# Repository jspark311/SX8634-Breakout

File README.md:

# SX8634-Breakout

A breakout board for Semtech's SX8634 capacitive touch sensor.

#### [Hackaday.io Page](https://hackaday.io/project/166853-sx8634-touch-sensor-breakout)

#### [Order from Tindie](https://www.tindie.com/products/17862/)

#### [Arduino driver](https://github.com/jspark311/Arduino-SX8634)

------------------------

### What is in this repository:

**./doc**:  Location for documentation

**./KiCAD**:  Hardware design files

**./lib**:  Third-party libraries

**./main**:  The optional provisioning program

**./downloadDeps.sh**   A script to download dependencies

------------------------

### Building the provisioning program

The provisioning program is intended to be run on an ESP32 devkit-C or comparable. It can be built by doing...

    ./downloadDeps.sh
    make

Then, flash it to the ESP32 board....

    make flash monitor

------------------------

Front | Back
:-------:|:------:
  |

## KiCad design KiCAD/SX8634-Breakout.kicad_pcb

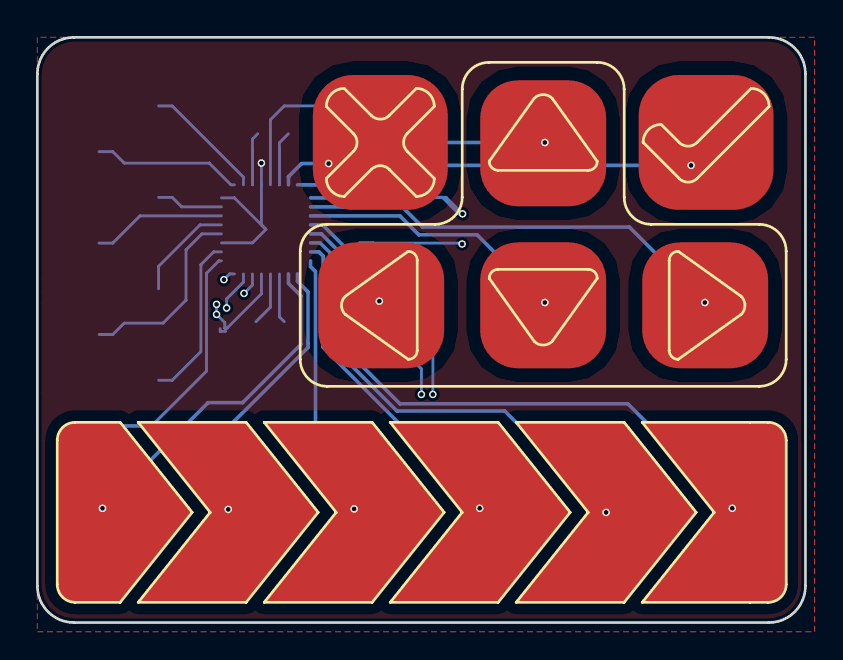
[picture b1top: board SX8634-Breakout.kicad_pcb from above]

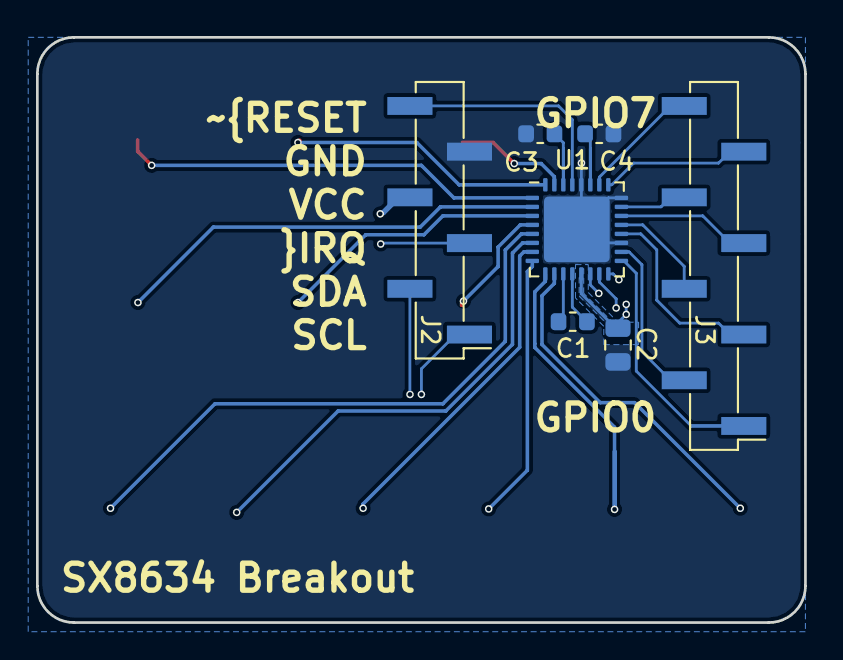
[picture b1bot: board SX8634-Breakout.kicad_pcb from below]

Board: 4 copper layers, 42.7 x 32.5 mm, 9 parts (7 on the bottom side), 30 nets.

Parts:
C1: 1nF; C_0603_1608Metric
C2: 100uF; C_0805_2012Metric
C3, C4: 100nF; C_0603_1608Metric
J1: Conn_01x12_Male; Cap-Touch_pattern_compact
J2: Conn_01x06; PinHeader_1x06_P2.54mm_Vertical_SMD_Pin1Left
J3: Conn_01x08; PinHeader_1x08_P2.54mm_Vertical_SMD_Pin1Left
P1: CONN_01X01; ManuvrLogo
U1: SX8634; QFN-32-1EP_5x5mm_P0.5mm_EP3.65x3.65mm

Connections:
/GPIO0: J3.1, U1.17
/GPIO1: J3.2, U1.18
/GPIO2: J3.3, U1.20
/GPIO3: J3.4, U1.21
/GPIO4: J3.5, U1.22
/GPIO5: J3.6, U1.23
/GPIO6: J3.7, U1.25
/GPIO7: J3.8, U1.26
/I2C_SCL: J2.1, U1.15
/I2C_SDA: J2.2, U1.16
/VCC: C2.1, J2.4, U1.13
/cap0: J1.6, U1.31
/cap1: J1.1, U1.32
/cap2: J1.5, U1.1
/cap3: J1.4, U1.2
/cap4: J1.2, U1.3
/cap5: J1.3, U1.4
/cap6: J1.12, U1.5
/cap7: J1.11, U1.6
/cap8: J1.10, U1.7
/cap9: J1.9, U1.8
/cap10: J1.8, U1.9
/cap11: J1.7, U1.10
/~Touch_IRQ: J2.3, U1.14
/~Touch_Reset: J2.6, U1.29
GND: C2.2, C3.1, C4.1, J2.5, U1.19, U1.24, U1.28, U1.33
unnamed: C1.1, U1.12
unnamed: C1.2, U1.11
unnamed: C3.2, U1.30
unnamed: C4.2, U1.27

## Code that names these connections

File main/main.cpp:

/**
* SX8634 provisioner
*
* This is Ian's tool for provisioning and testing Manuvr's touch boards. It is
*   being provided to inform the efforts of intrepid users who want to burn a
*   customized configuration to their board's non-volatile memory (NVM).
*
* This process is only needed if...
*   1) The GPIO pins are used as inputs, and the circuit can't abide pin contention.
*   2) The default settings are in some other way inadequate and instant-on is desired.
*
* If these cases don't apply to a given application, the boards can be used as-is.
* The only thing special about this program are the build-time options...
* #define CONFIG_MANUVR_SX8634         // Needed in any application using the touch board.
* #define CONFIG_SX8634_PROVISIONING   // Only needed to provision.
*
* A finished application would use CONFIG_MANUVR_SX8634, and possibly also
*   CONFIG_SX8634_CONFIG_ON_FAITH.
*
* CONFIG_SX8634_CONFIG_ON_FAITH causes the driver to skip the step of reading
*   the configuration from the chip on every boot. During this time, the chip
*   will be unresponsive to touch, and most applications will already know what
*   the loaded configuration will be. Using this option requires the config to
*   be provided to the driver during instantiation. The program will fail at
*   runtime if this configuration is not provided.
*
* Burning the NVM requires that the part be run a little bit hotter than the
*   rest of the system (3.6v). So the hardware needs to respect that fact also.
*   Trying to burn the NVM outside of this voltage range doesn't appear to cause
*   any damage, but it won't actually burn the NVM, and the chip won't tell you
*   why it failed. So it's on the user to ensure the voltage is adequate.
* The provisioning hardware level-shifts the GPIO pins for the sake of testing
*   the boards.
*
* Pins
* -------------
* IO33   SX8634 reset pin via level-shifter
* IO35   SX8634 IRQ pin via level-shifter with 3.3v pullup
* IO32   SCL
* IO25   SDA
*
* IO23   3.6v regulator enable line
* IO13   SX8634 GPIO0 via level-shifter
* IO14   SX8634 GPIO1 via level-shifter
* IO27   SX8634 GPIO2 via level-shifter
* IO26   SX8634 GPIO3 via level-shifter
* IO18   SX8634 GPIO4 via level-shifter
* IO19   SX8634 GPIO5 via level-shifter
* IO22   SX8634 GPIO6 via level-shifter
* IO21   SX8634 GPIO7 via level-shifter
*/

#include <math.h>

#include <Platform/Platform.h>
#include <Platform/Peripherals/I2C/I2CAdapter.h>
#include <XenoSession/Console/ManuvrConsole.h>
#include <Drivers/SX8634/SX8634.h>
#include "SX8634BitDiddler.h"

#ifdef __cplusplus
extern "C" {
#endif

#include <string.h>
#include <time.h>
#include <sys/time.h>
#include "freertos/FreeRTOS.h"
#include "freertos/task.h"
#include "freertos/event_groups.h"
#include "freertos/queue.h"

#include "rom/ets_sys.h"
#include "soc/dport_reg.h"
#include "soc/io_mux_reg.h"
#include "soc/rtc_cntl_reg.h"
#include "soc/gpio_reg.h"
#include "soc/gpio_sig_map.h"
#include "rom/gpio.h"
#include "driver/gpio.h"

#include "esp_system.h"
#include "esp_event_loop.h"
#include "esp_log.h"
#include "esp_attr.h"
#include "esp_sleep.h"
#include "nvs_flash.h"

#include "esp_task_wdt.h"
#include "esp_err.h"
#include "esp_event.h"


const I2CAdapterOptions i2c_opts(
  0,   // Device number
  25,  // sda
  32,  // scl
  0,   // No pullups.
  400000
);

/*
* If we care to setup the SX8634 differently than it comes shipped, we need to
*   provide a binary blob containing the parameters we want. Since this setup
*   takes time, and has implications for circuit safety, this blob ought to be
*   provisioned into the NVM once it is finalized for a given application.
* Only non-reserved values should be placed in the blob (97 bytes). Specifying
*   reserved bytes will have undefined (possibly disasterous) results. Nor
*   should the CRC value be supplied.
* If the NVM has already been written with the desired data, or the existing
*   configuration is the desired one, then this blob, and its reference in the
*   SX8634Opts, can be omitted and class will accept the existing config.
*/
const uint8_t sx8634_conf[97] = {
  0x2b, 0x02, 0x0E, 0x05, 0x01, 0xaa, 0xa5, 0x55, 0x00, 0x00, 0x00, 0x00, 0x00, 0x00,
  0xa0, 0xa0, 0xa0, 0xa0, 0xa0, 0xa0, 0xa0, 0xa0, 0xa0, 0xa0, 0xa0, 0xa0, 0x00, 0x30,
  0x50, 0x50, 0x01, 0x0a, 0x00, 0x00, 0x00, 0x03, 0x01, 0x80, 0x50, 0x50, 0x01, 0x02,
  0x00, 0x00, 0x00, 0x00, 0x00, 0x00, 0x00, 0xcd, 0x30, 0x00, 0x00, 0x3f, 0x02,

  0x56, 0xA0, // GPIO mode
  0x00, // pwrup state
  0x00, // autolight
  0x00, // polarity
  0xff, 0xff, 0xff, 0xff, 0xff, 0xff, 0xff, 0xff, // GPIO intensity ON
  0x00, 0x00, 0x00, 0x00, 0x00, 0x00, 0x00, 0x00, // GPIO intensity OFF
  0x00, // GPIO fxn
  0x00, // Increment factor
  0x00, // Decrement factor
  0x00, 0x00, 0x00, 0x00, // Increment time
  0x44, 0x40, 0x00, 0x00, // Decrement time
  0x00, 0x00, 0x00, 0x00, // Off delay
  0x00, 0x00, // Pull resistors
  0x01, 0x70, // Interrupt
  0x00, // Debounce
  0x74
};


/*
* The given i2c address will be used in preference to the value given in the
*   config blob. So give the address that the driver should use. Not the one the
*   driver ought to provision the boards with.
*/
const SX8634Opts sx8634_opts(
  SX8634_DEFAULT_I2C_ADDR,   // i2c addr
  33,     // Reset pin
  17,     // IRQ pin
  nullptr // sx8634_conf
);


/*******************************************************************************
* Main thread                                                                  *
*******************************************************************************/

void manuvr_task(void* pvParameter) {
  Kernel* kernel = platform.kernel();
  unsigned long ms_0 = millis();
  unsigned long ms_1 = ms_0;
  bool odd_even = false;

  I2CAdapter i2c(&i2c_opts);
  kernel->subscribe(&i2c);

  SX8634BitDiddler provisioner(&i2c, 23, 13, 14, 27, 26, 18, 19, 22, 21, &sx8634_opts);
  kernel->subscribe(&provisioner);

  while (1) {
    kernel->procIdleFlags();
    ms_1 = millis();
    kernel->advanceScheduler(ms_1 - ms_0);
    ms_0 = ms_1;
    odd_even = !odd_even;
    if (0 == kernel->procIdleFlags()) {
      vTaskDelay(10 / portTICK_PERIOD_MS);
    }
  }
}



/*******************************************************************************
* Main function                                                                *
*******************************************************************************/
void app_main() {
  /*
  * The platform object is created on the stack, but takes no action upon
  *   construction. The first thing that should be done is to call the preinit
  *   function to setup the defaults of the platform.
  */
  platform.platformPreInit();
  platform.bootstrap();

  xTaskCreate(manuvr_task, "_manuvr", 32768, NULL, (tskIDLE_PRIORITY + 2), NULL);
}

#ifdef __cplusplus
}
#endif

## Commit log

2019-08-09 Adding KiCAD files.
2019-08-09 Removing fab files.
2019-08-09 Adding files and finishing up.
2019-08-17 Adding provisioner.
2019-08-17 Updating meta.
2019-08-17 Keeping pace with Manuvr.
2019-08-17 Keeping pace with Manuvr. New features.
2019-08-19 Preparing for Arduino driver. Adding some reliability and provisioning features.
2019-08-21 Changing design for the sake of a cap array going obsolete.
2019-08-21 Fixing a naming mistake. Updating README.
2019-08-21 Adding arduino boilerplate and an unported driver.
2019-09-10 Removed obsoleted cap array.
2019-09-14 Adding Arduino driver and example. Not working yet.
2019-09-16 Provisioning jig changes.
2019-09-17 More provisioner improvments.
2019-09-19 Small tweaks.
2019-09-29 Library compiles, but Fails to read SPM. Sync Arduino i2c API is simpler. Driver will lose more complexity.
2019-09-29 Adding callback support.
2019-09-29 Fixes to ISR handler. Class works now.
2019-09-29 Fixed alignment bug for callbacks.
2019-10-08 Updating board images and README. Arduino driver is working.
2019-12-22 Changing demo config. Fixing name.
2020-02-22 Arduino driver is now in the Library manager.
